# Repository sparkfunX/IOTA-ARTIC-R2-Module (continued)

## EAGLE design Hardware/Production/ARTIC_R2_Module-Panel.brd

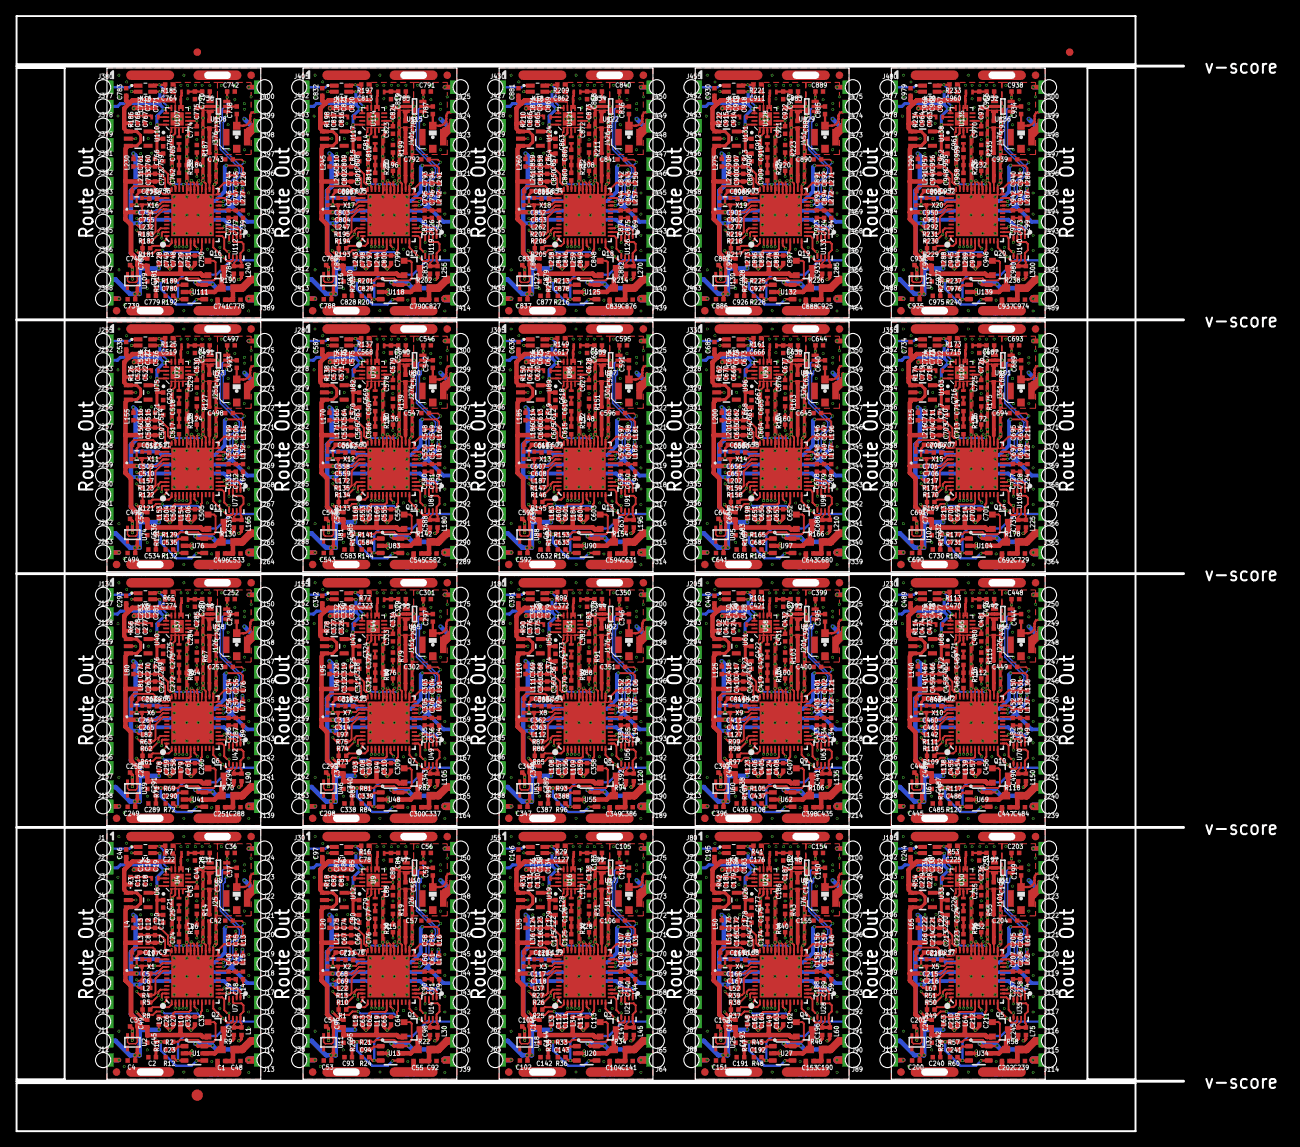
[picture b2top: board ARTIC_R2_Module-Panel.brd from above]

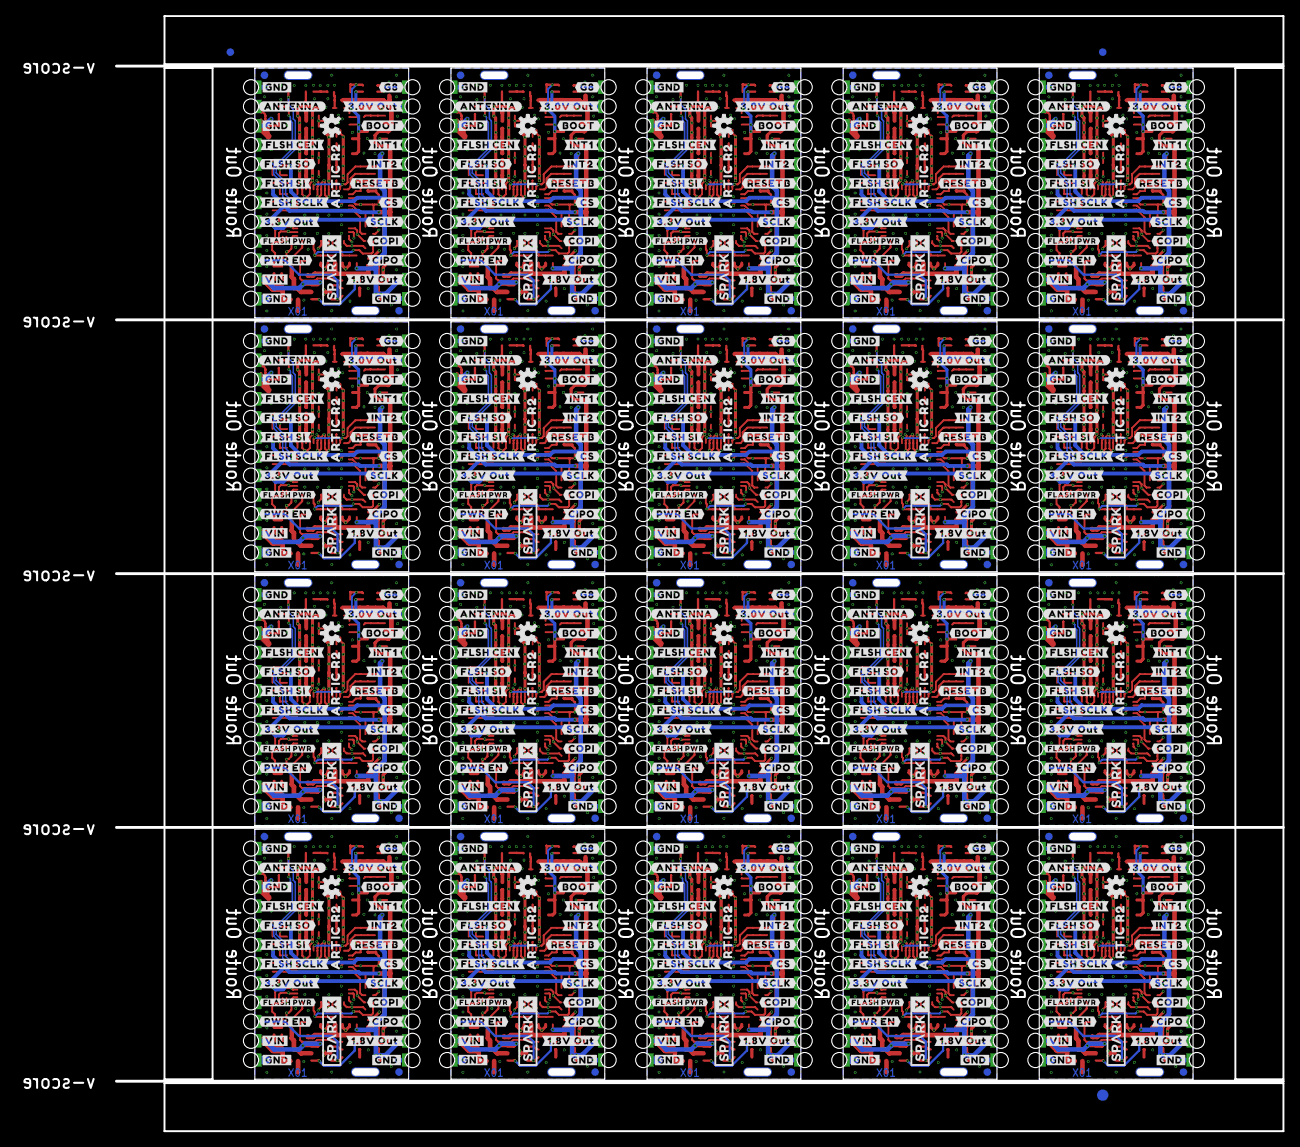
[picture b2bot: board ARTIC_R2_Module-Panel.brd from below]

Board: 4 copper layers, 154.2 x 147.3 mm, 2886 parts (583 on the bottom side), 1140 nets.

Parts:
C1, C15, C16, C20, C44, C45, C55, C80, C82, C86, C89, C95, C104, C129, C131, C135, C138, C144, C153, C178, C180, C184, C187, C193, C202, C227, C229, C233, C236, C242, C251, C276, C278, C282, C285, C291, C300, C325, C327, C331, C334, C340, C349, C374, C376, C380, C383, C389, C398, C423, C425, C429, C432, C438, C447, C472, C474, C478, C481, C487, C496, C521, C523, C527, C530, C536, C545, C570, C572, C576, C579, C585, C594, C619, C621, C625, C628, C634, C643, C668, C670, C674, C677, C683, C692, C717, C719, C723, C726, C732, C741, C766, C768, C772, C775, C781, C790, C815, C817, C821, C824, C830, C839, C864, C866, C870, C873, C879, C888, C913, C915, C919, C922, C928, C937, C962, C964, C968, C971, C977: 2.2uF; 0402-TIGHT
C2, C93, C142, C191, C240, C289, C338, C387, C436, C485, C534, C583, C632, C681, C730, C779, C828, C877, C926, C975: 10nF; 0402-TIGHT
C3, C4, C9, C12, C23, C46, C53, C54, C70, C74, C94, C97, C102, C103, C119, C123, C143, C146, C151, C152, C168, C172, C192, C195, C200, C201, C217, C221, C241, C244, C249, C250, C266, C270, C290, C293, C298, C299, C315, C319, C339, C342, C347, C348, C364, C368, C388, C391, C396, C397, C413, C417, C437, C440, C445, C446, C462, C466, C486, C489, C494, C495, C511, C515, C535, C538, C543, C544, C560, C564, C584, C587, C592, C593, C609, C613, C633, C636, C641, C642, C658, C662, C682, C685, C690, C691, C707, C711, C731, C734, C739, C740, C756, C760, C780, C783, C788, C789, C805, C809, C829, C832, C837, C838, C854, C858, C878, C881, C886, C887, C903, C907, C927, C930, C935, C936, C952, C956, C976, C979: 1.0uF; 0402-TIGHT
C5, C7, C18, C27, C33, C34, C39, C40, C58, C60, C62, C64, C66, C68, C81, C90, C107, C109, C111, C113, C115, C117, C130, C139, C156, C158, C160, C162, C164, C166, C179, C188, C205, C207, C209, C211, C213, C215, C228, C237, C254, C256, C258, C260, C262, C264, C277, C286, C303, C305, C307, C309, C311, C313, C326, C335, C352, C354, C356, C358, C360, C362, C375, C384, C401, C403, C405, C407, C409, C411, C424, C433, C450, C452, C454, C456, C458, C460, C473, C482, C499, C501, C503, C505, C507, C509, C522, C531, C548, C550, C552, C554, C556, C558, C571, C580, C597, C599, C601, C603, C605, C607, C620, C629, C646, C648, C650, C652, C654, C656, C669, C678, C695, C697, C699, C701, C703, C705, C718, C727, C744, C746, C748, C750, C752, C754, C767, C776, C793, C795, C797, C799, C801, C803, C816, C825, C842, C844, C846, C848, C850, C852, C865, C874, C891, C893, C895, C897, C899, C901, C914, C923, C940, C942, C944, C946, C948, C950, C963, C972: 22pF; 0402-TIGHT
C6, C8, C26, C32, C35, C38, C41, C48, C49, C50, C59, C61, C63, C65, C67, C69, C91, C92, C96, C98, C108, C110, C112, C114, C116, C118, C140, C141, C145, C147, C157, C159, C161, C163, C165, C167, C189, C190, C194, C196, C206, C208, C210, C212, C214, C216, C238, C239, C243, C245, C255, C257, C259, C261, C263, C265, C287, C288, C292, C294, C304, C306, C308, C310, C312, C314, C336, C337, C341, C343, C353, C355, C357, C359, C361, C363, C385, C386, C390, C392, C402, C404, C406, C408, C410, C412, C434, C435, C439, C441, C451, C453, C455, C457, C459, C461, C483, C484, C488, C490, C500, C502, C504, C506, C508, C510, C532, C533, C537, C539, C549, C551, C553, C555, C557, C559, C581, C582, C586, C588, C598, C600, C602, C604, C606, C608, C630, C631, C635, C637, C647, C649, C651, C653, C655, C657, C679, C680, C684, C686, C696, C698, C700, C702, C704, C706, C728, C729, C733, C735, C745, C747, C749, C751, C753, C755, C777, C778, C782, C784, C794, C796, C798, C800, C802, C804, C826, C827, C831, C833, C843, C845, C847, C849, C851, C853, C875, C876, C880, C882, C892, C894, C896, C898, C900, C902, C924, C925, C929, C931, C941, C943, C945, C947, C949, C951, C973, C974, C978, C980: 0.1uF; 0402-TIGHT
C10, C71, C120, C169, C218, C267, C316, C365, C414, C463, C512, C561, C610, C659, C708, C757, C806, C855, C904, C953: 47nF; 0402-TIGHT
C11, C19, C21, C22, C24, C25, C30, C31, C36, C37, C42, C43, C47, C51, C52, C56, C57, C73, C76, C77, C78, C79, C85, C88, C99, C100, C101, C105, C106, C122, C125, C126, C127, C128, C134, C137, C148, C149, C150, C154, C155, C171, C174, C175, C176, C177, C183, C186, C197, C198, C199, C203, C204, C220, C223, C224, C225, C226, C232, C235, C246, C247, C248, C252, C253, C269, C272, C273, C274, C275, C281, C284, C295, C296, C297, C301, C302, C318, C321, C322, C323, C324, C330, C333, C344, C345, C346, C350, C351, C367, C370, C371, C372, C373, C379, C382, C393, C394, C395, C399, C400, C416, C419, C420, C421, C422, C428, C431, C442, C443, C444, C448, C449, C465, C468, C469, C470, C471, C477, C480, C491, C492, C493, C497, C498, C514, C517, C518, C519, C520, C526, C529, C540, C541, C542, C546, C547, C563, C566, C567, C568, C569, C575, C578, C589, C590, C591, C595, C596, C612, C615, C616, C617, C618, C624, C627, C638, C639, C640, C644, C645, C661, C664, C665, C666, C667, C673, C676, C687, C688, C689, C693, C694, C710, C713, C714, C715, C716, C722, C725, C736, C737, C738, C742, C743, C759, C762, C763, C764, C765, C771, C774, C785, C786, C787, C791, C792, C808, C811, C812, C813, C814, C820, C823, C834, C835, C836, C840, C841, C857, C860, C861, C862, C863, C869, C872, C883, C884, C885, C889, C890, C906, C909, C910, C911, C912, C918, C921, C932, C933, C934, C938, C939, C955, C958, C959, C960, C961, C967, C970: 100pF; 0402-TIGHT
C13, C14, C75, C87, C124, C136, C173, C185, C222, C234, C271, C283, C320, C332, C369, C381, C418, C430, C467, C479, C516, C528, C565, C577, C614, C626, C663, C675, C712, C724, C761, C773, C810, C822, C859, C871, C908, C920, C957, C969: 10uF; 0402-TIGHT
C17, C72, C121, C170, C219, C268, C317, C366, C415, C464, C513, C562, C611, C660, C709, C758, C807, C856, C905, C954: 1.0nF; 0402-TIGHT
C28, C84, C133, C182, C231, C280, C329, C378, C427, C476, C525, C574, C623, C672, C721, C770, C819, C868, C917, C966: 9.1pF; 0402-TIGHT
C29, C83, C132, C181, C230, C279, C328, C377, C426, C475, C524, C573, C622, C671, C720, C769, C818, C867, C916, C965: 2.4 pF; 0402_MURATA
E$1, E$2, E$3, E$4: FIDUCIAL-1X2
E$5, E$6: FIDUCIAL-1.5X3
FD1, FD2, FD3, FD4, FD5, FD6, FD7, FD8, FD9, FD10, FD11, FD12, FD13, FD14, FD15, FD16, FD17, FD18, FD19, FD20, FD21, FD22, FD23, FD24, FD25, FD26, FD27, FD28, FD29, FD30, FD31, FD32, FD33, FD34, FD35, FD36, FD37, FD38, FD39, FD40, FD41, FD42, FD43, FD44, FD45, FD46, FD47, FD48, FD49, FD50, FD51, FD52, FD53, FD54, FD55, FD56, FD57, FD58, FD59, FD60, FD61, FD62, FD63, FD64, FD65, FD66, FD67, FD68, FD69, FD70, FD71, FD72, FD73, FD74, FD75, FD76, FD77, FD78, FD79, FD80: FIDUCIAL1X2; FIDUCIAL-1X2
J1, J2, J3, J4, J5, J6, J7, J8, J9, J10, J11, J12, J13, J14, J15, J16, J17, J18, J19, J20, J21, J22, J23, J24, J27, J28, J29, J30, J31, J32, J33, J34, J35, J36, J37, J38, J39, J40, J41, J42, J43, J44, J45, J46, J47, J48, J49, J50, J52, J53, J54, J55, J56, J57, J58, J59, J60, J61, J62, J63, J64, J65, J66, J67, J68, J69, J70, J71, J72, J73, J74, J75, J77, J78, J79, J80, J81, J82, J83, J84, J85, J86, J87, J88, J89, J90, J91, J92, J93, J94, J95, J96, J97, J98, J99, J100, J102, J103, J104, J105, J106, J107, J108, J109, J110, J111, J112, J113, J114, J115, J116, J117, J118, J119, J120, J121, J122, J123, J124, J125, J127, J128, J129, J130, J131, J132, J133, J134, J135, J136, J137, J138, J139, J140, J141, J142, J143, J144, J145, J146, J147, J148, J149, J150, J152, J153, J154, J155, J156, J157, J158, J159, J160, J161, J162, J163, J164, J165, J166, J167, J168, J169, J170, J171, J172, J173, J174, J175, J177, J178, J179, J180, J181, J182, J183, J184, J185, J186, J187, J188, J189, J190, J191, J192, J193, J194, J195, J196, J197, J198, J199, J200, J202, J203, J204, J205, J206, J207, J208, J209, J210, J211, J212, J213, J214, J215, J216, J217, J218, J219, J220, J221, J222, J223, J224, J225, J227, J228, J229, J230, J231, J232, J233, J234, J235, J236, J237, J238, J239, J240, J241, J242, J243, J244, J245, J246, J247, J248, J249, J250, J252, J253, J254, J255, J256, J257, J258, J259, J260, J261, J262, J263, J264, J265, J266, J267, J268, J269, J270, J271, J272, J273, J274, J275, J277, J278, J279, J280, J281, J282, J283, J284, J285, J286, J287, J288, J289, J290, J291, J292, J293, J294, J295, J296, J297, J298, J299, J300, J302, J303, J304, J305, J306, J307, J308, J309, J310, J311, J312, J313, J314, J315, J316, J317, J318, J319, J320, J321, J322, J323, J324, J325, J327, J328, J329, J330, J331, J332, J333, J334, J335, J336, J337, J338, J339, J340, J341, J342, J343, J344, J345, J346, J347, J348, J349, J350, J352, J353, J354, J355, J356, J357, J358, J359, J360, J361, J362, J363, J364, J365, J366, J367, J368, J369, J370, J371, J372, J373, J374, J375, J377, J378, J379, J380, J381, J382, J383, J384, J385, J386, J387, J388, J389, J390, J391, J392, J393, J394, J395, J396, J397, J398, J399, J400, J402, J403, J404, J405, J406, J407, J408, J409, J410, J411, J412, J413, J414, J415, J416, J417, J418, J419, J420, J421, J422, J423, J424, J425, J427, J428, J429, J430, J431, J432, J433, J434, J435, J436, J437, J438, J439, J440, J441, J442, J443, J444, J445, J446, J447, J448, J449, J450, J452, J453, J454, J455, J456, J457, J458, J459, J460, J461, J462, J463, J464, J465, J466, J467, J468, J469, J470, J471, J472, J473, J474, J475, J477, J478, J479, J480, J481, J482, J483, J484, J485, J486, J487, J488, J489, J490, J491, J492, J493, J494, J495, J496, J497, J498, J499, J500: CONN_01_CASTELLATED_4LAYER
J25, J26, J51, J76, J101, J126, J151, J176, J201, J226, J251, J276, J301, J326, J351, J376, J401, J426, J451, J476: U.FL
K1, K2, K3, K4, K5, K6, K7, K8, K9, K10, K11, K12, K13, K14, K15, K16, K17, K18, K19, K20: TLP3475R; TLP3475RTPF
L1, L2, L3, L4, L9, L10, L13, L14, L15, L16, L17, L18, L19, L20, L21, L22, L29, L30, L31, L32, L33, L34, L35, L36, L37, L44, L45, L46, L47, L48, L49, L50, L51, L52, L59, L60, L61, L62, L63, L64, L65, L66, L67, L74, L75, L76, L77, L78, L79, L80, L81, L82, L89, L90, L91, L92, L93, L94, L95, L96, L97, L104, L105, L106, L107, L108, L109, L110, L111, L112, L119, L120, L121, L122, L123, L124, L125, L126, L127, L134, L135, L136, L137, L138, L139, L140, L141, L142, L149, L150, L151, L152, L153, L154, L155, L156, L157, L164, L165, L166, L167, L168, L169, L170, L171, L172, L179, L180, L181, L182, L183, L184, L185, L186, L187, L194, L195, L196, L197, L198, L199, L200, L201, L202, L209, L210, L211, L212, L213, L214, L215, L216, L217, L224, L225, L226, L227, L228, L229, L230, L231, L232, L239, L240, L241, L242, L243, L244, L245, L246, L247, L254, L255, L256, L257, L258, L259, L260, L261, L262, L269, L270, L271, L272, L273, L274, L275, L276, L277, L284, L285, L286, L287, L288, L289, L290, L291, L292, L299, L300: 30Ω; 0402-TIGHT
L5, L24, L39, L54, L69, L84, L99, L114, L129, L144, L159, L174, L189, L204, L219, L234, L249, L264, L279, L294: 15nH; 0402_COILCRAFT
L6, L25, L40, L55, L70, L85, L100, L115, L130, L145, L160, L175, L190, L205, L220, L235, L250, L265, L280, L295: 27nH; 0402_COILCRAFT
L7, L23, L38, L53, L68, L83, L98, L113, L128, L143, L158, L173, L188, L203, L218, L233, L248, L263, L278, L293: 18nH; 0402_COILCRAFT
L8, L26, L41, L56, L71, L86, L101, L116, L131, L146, L161, L176, L191, L206, L221, L236, L251, L266, L281, L296: 12nH; 0402_COILCRAFT
L11, L27, L42, L57, L72, L87, L102, L117, L132, L147, L162, L177, L192, L207, L222, L237, L252, L267, L282, L297: 30nH; 0402_COILCRAFT
L12, L28, L43, L58, L73, L88, L103, L118, L133, L148, L163, L178, L193, L208, L223, L238, L253, L268, L283, L298: 51nH; 0402_COILCRAFT
LOGO1, LOGO2, LOGO3, LOGO4, LOGO5, LOGO6, LOGO7, LOGO8, LOGO9, LOGO10, LOGO11, LOGO12, LOGO13, LOGO14, LOGO15, LOGO16, LOGO17, LOGO18, LOGO19, LOGO20: OSHW-LOGOS; OSHW-LOGO-S
Q1, Q2, Q3, Q4, Q5, Q6, Q7, Q8, Q9, Q10, Q11, Q12, Q13, Q14, Q15, Q16, Q17, Q18, Q19, Q20: 5.8A/30V/35mΩ; SOT23-3
R1, R5, R8, R10, R25, R26, R37, R38, R49, R50, R61, R62, R73, R74, R85, R86, R97, R98, R109, R110, R121, R122, R133, R134, R145, R146, R157, R158, R169, R170, R181, R182, R193, R194, R205, R206, R217, R218, R229, R230: 100k; 0402-TIGHT
R2, R11, R21, R23, R33, R35, R45, R47, R57, R59, R69, R71, R81, R83, R93, R95, R105, R107, R117, R119, R129, R131, R141, R143, R153, R155, R165, R167, R177, R179, R189, R191, R201, R203, R213, R215, R225, R227, R237, R239: 100OHM; 0402-TIGHT
R3, R18, R30, R42, R54, R66, R78, R90, R102, R114, R126, R138, R150, R162, R174, R186, R198, R210, R222, R234: 3.9OHM; 0402-TIGHT
R4, R13, R27, R39, R51, R63, R75, R87, R99, R111, R123, R135, R147, R159, R171, R183, R195, R207, R219, R231: 33k; 0402-TIGHT
R6, R15, R28, R40, R52, R64, R76, R88, R100, R112, R124, R136, R148, R160, R172, R184, R196, R208, R220, R232: 220OHM; 0402-TIGHT
R7, R12, R16, R24, R29, R36, R41, R48, R53, R60, R65, R72, R77, R84, R89, R96, R101, R108, R113, R120, R125, R132, R137, R144, R149, R156, R161, R168, R173, R180, R185, R192, R197, R204, R209, R216, R221, R228, R233, R240: 10k; 0402-TIGHT
R9, R22, R34, R46, R58, R70, R82, R94, R106, R118, R130, R142, R154, R166, R178, R190, R202, R214, R226, R238: 0.1R; 0603
R14, R19, R31, R43, R55, R67, R79, R91, R103, R115, R127, R139, R151, R163, R175, R187, R199, R211, R223, R235: 470; 0402-TIGHT
R17, R20, R32, R44, R56, R68, R80, R92, R104, R116, R128, R140, R152, R164, R176, R188, R200, R212, R224, R236: 47; 0402-TIGHT
SCREEN, SCREEN1, SCREEN2, SCREEN3, SCREEN4, SCREEN5, SCREEN6, SCREEN7, SCREEN8, SCREEN9, SCREEN10, SCREEN11, SCREEN12, SCREEN13, SCREEN14, SCREEN15, SCREEN16, SCREEN17, SCREEN18, SCREEN19: ARTIC_R2_CASTELLATED_CAN; ARTIC_R2_CASTELLATED
SPARKX1, SPARKX2, SPARKX3, SPARKX4, SPARKX5, SPARKX6, SPARKX7, SPARKX8, SPARKX9, SPARKX10, SPARKX11, SPARKX12, SPARKX13, SPARKX14, SPARKX15, SPARKX16, SPARKX17, SPARKX18, SPARKX19, SPARKX20: SPARKX-LOGO4; SPARKX-MEDIUM
U1, U13, U20, U27, U34, U41, U48, U55, U62, U69, U76, U83, U90, U97, U104, U111, U118, U125, U132, U139: ADM4210-1; TSOT6
U2, U11, U18, U25, U32, U39, U46, U53, U60, U67, U74, U81, U88, U95, U102, U109, U116, U123, U130, U137: 1.8V/100mA; SC70
U3, U8, U15, U22, U29, U36, U43, U50, U57, U64, U71, U78, U85, U92, U99, U106, U113, U120, U127, U134: ARTIC_R2; QFN-48
U4, U9, U16, U23, U30, U37, U44, U51, U58, U65, U72, U79, U86, U93, U100, U107, U114, U121, U128, U135: RFPA0133; QFN50P300X300X86-17N
U5, U10, U17, U24, U31, U38, U45, U52, U59, U66, U73, U80, U87, U94, U101, U108, U115, U122, U129, U136: AS179-92LF; SOT65P220X100-6N
U6, U12, U19, U26, U33, U40, U47, U54, U61, U68, U75, U82, U89, U96, U103, U110, U117, U124, U131, U138: 3.0V; SOT23-5
U7, U14, U21, U28, U35, U42, U49, U56, U63, U70, U77, U84, U91, U98, U105, U112, U119, U126, U133, U140: SST25VF020BUSON; USON_3X2MM
U$1, U$3, U$4, U$5, U$28, U$29, U$30, U$31, U$54, U$55, U$56, U$57, U$80, U$81, U$82, U$83, U$106, U$107, U$108, U$109, U$132, U$133, U$134, U$135, U$158, U$159, U$160, U$161, U$184, U$185, U$186, U$187, U$210, U$211, U$212, U$213, U$236, U$237, U$238, U$239, U$262, U$263, U$264, U$265, U$288, U$289, U$290, U$291, U$314, U$315, U$316, U$317, U$340, U$341, U$342, U$343, U$366, U$367, U$368, U$369, U$392, U$393, U$394, U$395, U$418, U$419, U$420, U$421, U$444, U$445, U$446, U$447, U$470, U$471, U$472, U$473, U$496, U$497, U$498, U$499: #GND#0
U$2, U$27, U$53, U$79, U$105, U$131, U$157, U$183, U$209, U$235, U$261, U$287, U$313, U$339, U$365, U$391, U$417, U$443, U$469, U$495: 10
U$6, U$32, U$58, U$84, U$110, U$136, U$162, U$188, U$214, U$240, U$266, U$292, U$318, U$344, U$370, U$396, U$422, U$448, U$474, U$500: #PWR_EN#0
U$7, U$33, U$59, U$85, U$111, U$137, U$163, U$189, U$215, U$241, U$267, U$293, U$319, U$345, U$371, U$397, U$423, U$449, U$475, U$501: #VIN#0
U$8, U$52, U$78, U$104, U$130, U$156, U$182, U$208, U$234, U$260, U$286, U$312, U$338, U$364, U$390, U$416, U$442, U$468, U$494, U$520: #FLASH_PWR#0
U$9, U$34, U$60, U$86, U$112, U$138, U$164, U$190, U$216, U$242, U$268, U$294, U$320, U$346, U$372, U$398, U$424, U$450, U$476, U$502: #FLSH_SCLK#0
U$10, U$35, U$61, U$87, U$113, U$139, U$165, U$191, U$217, U$243, U$269, U$295, U$321, U$347, U$373, U$399, U$425, U$451, U$477, U$503: #FLSH_SI#0
U$11, U$37, U$63, U$89, U$115, U$141, U$167, U$193, U$219, U$245, U$271, U$297, U$323, U$349, U$375, U$401, U$427, U$453, U$479, U$505: #FLSH_SO#0
U$12, U$36, U$62, U$88, U$114, U$140, U$166, U$192, U$218, U$244, U$270, U$296, U$322, U$348, U$374, U$400, U$426, U$452, U$478, U$504: #FLSH_CEN#0
U$13, U$38, U$64, U$90, U$116, U$142, U$168, U$194, U$220, U$246, U$272, U$298, U$324, U$350, U$376, U$402, U$428, U$454, U$480, U$506: #3#3V_OUT#0
U$14, U$39, U$65, U$91, U$117, U$143, U$169, U$195, U$221, U$247, U$273, U$299, U$325, U$351, U$377, U$403, U$429, U$455, U$481, U$507: #ANTENNA#0
U$15, U$40, U$66, U$92, U$118, U$144, U$170, U$196, U$222, U$248, U$274, U$300, U$326, U$352, U$378, U$404, U$430, U$456, U$482, U$508: #G8#0
U$16, U$41, U$67, U$93, U$119, U$145, U$171, U$197, U$223, U$249, U$275, U$301, U$327, U$353, U$379, U$405, U$431, U$457, U$483, U$509: #3#0V_OUT#0
U$17, U$42, U$68, U$94, U$120, U$146, U$172, U$198, U$224, U$250, U$276, U$302, U$328, U$354, U$380, U$406, U$432, U$458, U$484, U$510: #BOOT#0
U$18, U$43, U$69, U$95, U$121, U$147, U$173, U$199, U$225, U$251, U$277, U$303, U$329, U$355, U$381, U$407, U$433, U$459, U$485, U$511: #INT1#0
U$19, U$44, U$70, U$96, U$122, U$148, U$174, U$200, U$226, U$252, U$278, U$304, U$330, U$356, U$382, U$408, U$434, U$460, U$486, U$512: #INT2#0
U$20, U$45, U$71, U$97, U$123, U$149, U$175, U$201, U$227, U$253, U$279, U$305, U$331, U$357, U$383, U$409, U$435, U$461, U$487, U$513: #RESETB#0
U$21, U$46, U$72, U$98, U$124, U$150, U$176, U$202, U$228, U$254, U$280, U$306, U$332, U$358, U$384, U$410, U$436, U$462, U$488, U$514: #CS#0
U$22, U$47, U$73, U$99, U$125, U$151, U$177, U$203, U$229, U$255, U$281, U$307, U$333, U$359, U$385, U$411, U$437, U$463, U$489, U$515: #SCLK#0
U$23, U$48, U$74, U$100, U$126, U$152, U$178, U$204, U$230, U$256, U$282, U$308, U$334, U$360, U$386, U$412, U$438, U$464, U$490, U$516: #COPI#0
U$24, U$49, U$75, U$101, U$127, U$153, U$179, U$205, U$231, U$257, U$283, U$309, U$335, U$361, U$387, U$413, U$439, U$465, U$491, U$517: #CIPO#0
U$25, U$50, U$76, U$102, U$128, U$154, U$180, U$206, U$232, U$258, U$284, U$310, U$336, U$362, U$388, U$414, U$440, U$466, U$492, U$518: #1#8V_OUT#0
U$26, U$51, U$77, U$103, U$129, U$155, U$181, U$207, U$233, U$259, U$285, U$311, U$337, U$363, U$389, U$415, U$441, U$467, U$493, U$519: ARTIC_R20
X1, X2, X3, X4, X5, X6, X7, X8, X9, X10, X11, X12, X13, X14, X15, X16, X17, X18, X19, X20: CRYSTAL-TCXO-26MHZ; CRYSTAL-TCXO-SMD-1.65X1.25

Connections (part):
1.8V: C4.1, J11.1, L2.2, L4.2, L9.2, L13.2, L14.2, U2.5
1.8V1: C53.1, J37.1, L16.2, L18.2, L20.2, L22.2, L29.2, U11.5
1.8V2: C102.1, J62.1, L31.2, L33.2, L35.2, L37.2, L44.2, U18.5
1.8V3: C151.1, J87.1, L46.2, L48.2, L50.2, L52.2, L59.2, U25.5
1.8V4: C200.1, J112.1, L61.2, L63.2, L65.2, L67.2, L74.2, U32.5
1.8V5: C249.1, J137.1, L76.2, L78.2, L80.2, L82.2, L89.2, U39.5
1.8V6: C298.1, J162.1, L91.2, L93.2, L95.2, L97.2, L104.2, U46.5
1.8V7: C347.1, J187.1, L106.2, L108.2, L110.2, L112.2, L119.2, U53.5
1.8V8: C396.1, J212.1, L121.2, L123.2, L125.2, L127.2, L134.2, U60.5
1.8V9: C445.1, J237.1, L136.2, L138.2, L140.2, L142.2, L149.2, U67.5
1.8V10: C494.1, J262.1, L151.2, L153.2, L155.2, L157.2, L164.2, U74.5
1.8V11: C543.1, J287.1, L166.2, L168.2, L170.2, L172.2, L179.2, U81.5
1.8V12: C592.1, J312.1, L181.2, L183.2, L185.2, L187.2, L194.2, U88.5
1.8V13: C641.1, J337.1, L196.2, L198.2, L200.2, L202.2, L209.2, U95.5
1.8V14: C690.1, J362.1, L211.2, L213.2, L215.2, L217.2, L224.2, U102.5
1.8V15: C739.1, J387.1, L226.2, L228.2, L230.2, L232.2, L239.2, U109.5
1.8V16: C788.1, J412.1, L241.2, L243.2, L245.2, L247.2, L254.2, U116.5
1.8V17: C837.1, J437.1, L256.2, L258.2, L260.2, L262.2, L269.2, U123.5
1.8V18: C886.1, J462.1, L271.2, L273.2, L275.2, L277.2, L284.2, U130.5
1.8V19: C935.1, J487.1, L286.2, L288.2, L290.2, L292.2, L299.2, U137.5
ANTENNA: C37.1, J23.1, J25.FEED
ANTENNA1: C52.1, J26.FEED, J49.1
ANTENNA2: C101.1, J51.FEED, J74.1
ANTENNA3: C150.1, J76.FEED, J99.1
ANTENNA4: C199.1, J101.FEED, J124.1
ANTENNA5: C248.1, J126.FEED, J149.1
ANTENNA6: C297.1, J151.FEED, J174.1
ANTENNA7: C346.1, J176.FEED, J199.1
ANTENNA8: C395.1, J201.FEED, J224.1
ANTENNA9: C444.1, J226.FEED, J249.1
ANTENNA10: C493.1, J251.FEED, J274.1
ANTENNA11: C542.1, J276.FEED, J299.1
ANTENNA12: C591.1, J301.FEED, J324.1
ANTENNA13: C640.1, J326.FEED, J349.1
ANTENNA14: C689.1, J351.FEED, J374.1
ANTENNA15: C738.1, J376.FEED, J399.1
ANTENNA16: C787.1, J401.FEED, J424.1
ANTENNA17: C836.1, J426.FEED, J449.1
ANTENNA18: C885.1, J451.FEED, J474.1
ANTENNA19: C934.1, J476.FEED, J499.1
BOOT: J3.1, R5.1, U3.46
BOOT1: J28.1, R10.1, U8.46
BOOT2: J53.1, R26.1, U15.46
BOOT3: J78.1, R38.1, U22.46
BOOT4: J103.1, R50.1, U29.46
BOOT5: J128.1, R62.1, U36.46
BOOT6: J153.1, R74.1, U43.46
BOOT7: J178.1, R86.1, U50.46
BOOT8: J203.1, R98.1, U57.46
BOOT9: J228.1, R110.1, U64.46
BOOT10: J253.1, R122.1, U71.46
BOOT11: J278.1, R134.1, U78.46
BOOT12: J303.1, R146.1, U85.46
BOOT13: J328.1, R158.1, U92.46
BOOT14: J353.1, R170.1, U99.46
BOOT15: J378.1, R182.1, U106.46
BOOT16: J403.1, R194.1, U113.46
BOOT17: J428.1, R206.1, U120.46
BOOT18: J453.1, R218.1, U127.46
BOOT19: J478.1, R230.1, U134.46
CIPO: J10.1, U3.5
CIPO1: J36.1, U8.5
CIPO2: J61.1, U15.5
CIPO3: J86.1, U22.5
CIPO4: J111.1, U29.5
CIPO5: J136.1, U36.5
CIPO6: J161.1, U43.5
CIPO7: J186.1, U50.5
CIPO8: J211.1, U57.5
CIPO9: J236.1, U64.5
CIPO10: J261.1, U71.5
CIPO11: J286.1, U78.5
CIPO12: J311.1, U85.5
CIPO13: J336.1, U92.5
CIPO14: J361.1, U99.5
CIPO15: J386.1, U106.5
CIPO16: J411.1, U113.5
CIPO17: J436.1, U120.5
CIPO18: J461.1, U127.5
CIPO19: J486.1, U134.5
COPI: J9.1, U3.4
COPI1: J35.1, U8.4
COPI2: J60.1, U15.4
COPI3: J85.1, U22.4
COPI4: J110.1, U29.4
COPI5: J135.1, U36.4
COPI6: J160.1, U43.4
COPI7: J185.1, U50.4
COPI8: J210.1, U57.4
COPI9: J235.1, U64.4
COPI10: J260.1, U71.4
COPI11: J285.1, U78.4
COPI12: J310.1, U85.4
COPI13: J335.1, U92.4
COPI14: J360.1, U99.4
COPI15: J385.1, U106.4
COPI16: J410.1, U113.4
COPI17: J435.1, U120.4
COPI18: J460.1, U127.4
COPI19: J485.1, U134.4
CS: J7.1, U3.2
CS1: J33.1, U8.2
CS2: J58.1, U15.2
CS3: J83.1, U22.2
CS4: J108.1, U29.2
CS5: J133.1, U36.2
CS6: J158.1, U43.2
CS7: J183.1, U50.2
CS8: J208.1, U57.2
CS9: J233.1, U64.2
CS10: J258.1, U71.2
CS11: J283.1, U78.2
CS12: J308.1, U85.2
CS13: J333.1, U92.2
CS14: J358.1, U99.2
CS15: J383.1, U106.2
CS16: J408.1, U113.2
CS17: J433.1, U120.2
CS18: J458.1, U127.2
CS19: J483.1, U134.2
FLASH_PWR: J16.1, L1.2
FLASH_PWR1: J42.1, L30.2
FLASH_PWR2: J67.1, L45.2
FLASH_PWR3: J92.1, L60.2
FLASH_PWR4: J117.1, L75.2
FLASH_PWR5: J142.1, L90.2
FLASH_PWR6: J167.1, L105.2
FLASH_PWR7: J192.1, L120.2
FLASH_PWR8: J217.1, L135.2
FLASH_PWR9: J242.1, L150.2
FLASH_PWR10: J267.1, L165.2
FLASH_PWR11: J292.1, L180.2
FLASH_PWR12: J317.1, L195.2
FLASH_PWR13: J342.1, L210.2
FLASH_PWR14: J367.1, L225.2
FLASH_PWR15: J392.1, L240.2
FLASH_PWR16: J417.1, L255.2
FLASH_PWR17: J442.1, L270.2
FLASH_PWR18: J467.1, L285.2
FLASH_PWR19: J492.1, L300.2
FLASH_VCC: C50.1, L1.1, U7.3, U7.7, U7.8
FLASH_VCC1: C98.1, L30.1, U14.3, U14.7, U14.8
FLASH_VCC2: C147.1, L45.1, U21.3, U21.7, U21.8
FLASH_VCC3: C196.1, L60.1, U28.3, U28.7, U28.8
FLASH_VCC4: C245.1, L75.1, U35.3, U35.7, U35.8
FLASH_VCC5: C294.1, L90.1, U42.3, U42.7, U42.8
FLASH_VCC6: C343.1, L105.1, U49.3, U49.7, U49.8
FLASH_VCC7: C392.1, L120.1, U56.3, U56.7, U56.8
FLASH_VCC8: C441.1, L135.1, U63.3, U63.7, U63.8
FLASH_VCC9: C490.1, L150.1, U70.3, U70.7, U70.8
FLASH_VCC10: C539.1, L165.1, U77.3, U77.7, U77.8
FLASH_VCC11: C588.1, L180.1, U84.3, U84.7, U84.8
FLASH_VCC12: C637.1, L195.1, U91.3, U91.7, U91.8
FLASH_VCC13: C686.1, L210.1, U98.3, U98.7, U98.8
FLASH_VCC14: C735.1, L225.1, U105.3, U105.7, U105.8
FLASH_VCC15: C784.1, L240.1, U112.3, U112.7, U112.8
FLASH_VCC16: C833.1, L255.1, U119.3, U119.7, U119.8
FLASH_VCC17: C882.1, L270.1, U126.3, U126.7, U126.8
FLASH_VCC18: C931.1, L285.1, U133.3, U133.7, U133.8
FLASH_VCC19: C980.1, L300.1, U140.3, U140.7, U140.8
FLSH_CEN: J21.1, U3.15, U7.1
FLSH_CEN1: J47.1, U8.15, U14.1
FLSH_CEN2: J72.1, U15.15, U21.1
FLSH_CEN3: J97.1, U22.15, U28.1
FLSH_CEN4: J122.1, U29.15, U35.1
FLSH_CEN5: J147.1, U36.15, U42.1
FLSH_CEN6: J172.1, U43.15, U49.1
FLSH_CEN7: J197.1, U50.15, U56.1
FLSH_CEN8: J222.1, U57.15, U63.1
FLSH_CEN9: J247.1, U64.15, U70.1
FLSH_CEN10: J272.1, U71.15, U77.1
FLSH_CEN11: J297.1, U78.15, U84.1
FLSH_CEN12: J322.1, U85.15, U91.1
FLSH_CEN13: J347.1, U92.15, U98.1
FLSH_CEN14: J372.1, U99.15, U105.1
FLSH_CEN15: J397.1, U106.15, U112.1
FLSH_CEN16: J422.1, U113.15, U119.1
FLSH_CEN17: J447.1, U120.15, U126.1
FLSH_CEN18: J472.1, U127.15, U133.1
FLSH_CEN19: J497.1, U134.15, U140.1
FLSH_SCLK: J18.1, U3.12, U7.6
FLSH_SCLK1: J44.1, U8.12, U14.6
FLSH_SCLK2: J69.1, U15.12, U21.6
FLSH_SCLK3: J94.1, U22.12, U28.6
FLSH_SCLK4: J119.1, U29.12, U35.6
FLSH_SCLK5: J144.1, U36.12, U42.6
FLSH_SCLK6: J169.1, U43.12, U49.6
FLSH_SCLK7: J194.1, U50.12, U56.6
FLSH_SCLK8: J219.1, U57.12, U63.6
FLSH_SCLK9: J244.1, U64.12, U70.6
FLSH_SCLK10: J269.1, U71.12, U77.6
FLSH_SCLK11: J294.1, U78.12, U84.6
FLSH_SCLK12: J319.1, U85.12, U91.6
FLSH_SCLK13: J344.1, U92.12, U98.6
FLSH_SCLK14: J369.1, U99.12, U105.6
FLSH_SCLK15: J394.1, U106.12, U112.6
FLSH_SCLK16: J419.1, U113.12, U119.6
FLSH_SCLK17: J444.1, U120.12, U126.6
FLSH_SCLK18: J469.1, U127.12, U133.6
FLSH_SCLK19: J494.1, U134.12, U140.6
FLSH_SI: J19.1, U3.13, U7.5
FLSH_SI1: J45.1, U8.13, U14.5
FLSH_SI2: J70.1, U15.13, U21.5
FLSH_SI3: J95.1, U22.13, U28.5
FLSH_SI4: J120.1, U29.13, U35.5
FLSH_SI5: J145.1, U36.13, U42.5
FLSH_SI6: J170.1, U43.13, U49.5
FLSH_SI7: J195.1, U50.13, U56.5
FLSH_SI8: J220.1, U57.13, U63.5
FLSH_SI9: J245.1, U64.13, U70.5
FLSH_SI10: J270.1, U71.13, U77.5
FLSH_SI11: J295.1, U78.13, U84.5
FLSH_SI12: J320.1, U85.13, U91.5
FLSH_SI13: J345.1, U92.13, U98.5
FLSH_SI14: J370.1, U99.13, U105.5
FLSH_SI15: J395.1, U106.13, U112.5
FLSH_SI16: J420.1, U113.13, U119.5
FLSH_SI17: J445.1, U120.13, U126.5
FLSH_SI18: J470.1, U127.13, U133.5
FLSH_SI19: J495.1, U134.13, U140.5
FLSH_SO: J20.1, U3.14, U7.2
FLSH_SO1: J46.1, U8.14, U14.2
FLSH_SO2: J71.1, U15.14, U21.2
FLSH_SO3: J96.1, U22.14, U28.2
FLSH_SO4: J121.1, U29.14, U35.2
FLSH_SO5: J146.1, U36.14, U42.2
FLSH_SO6: J171.1, U43.14, U49.2
FLSH_SO7: J196.1, U50.14, U56.2
FLSH_SO8: J221.1, U57.14, U63.2
FLSH_SO9: J246.1, U64.14, U70.2
FLSH_SO10: J271.1, U71.14, U77.2
FLSH_SO11: J296.1, U78.14, U84.2
FLSH_SO12: J321.1, U85.14, U91.2
FLSH_SO13: J346.1, U92.14, U98.2
FLSH_SO14: J371.1, U99.14, U105.2
FLSH_SO15: J396.1, U106.14, U112.2
FLSH_SO16: J421.1, U113.14, U119.2
FLSH_SO17: J446.1, U120.14, U126.2
FLSH_SO18: J471.1, U127.14, U133.2
FLSH_SO19: J496.1, U134.14, U140.2
G1: J30.1, K2.1
G2: J55.1, K3.1
G3: J80.1, K4.1
G4: J105.1, K5.1
G5: J130.1, K6.1
G6: J155.1, K7.1
G7: J180.1, K8.1
G8: J1.1, K1.1
G9: J205.1, K9.1
G10: J230.1, K10.1
G11: J255.1, K11.1
G12: J280.1, K12.1
G13: J305.1, K13.1
G14: J330.1, K14.1
G15: J355.1, K15.1
G16: J380.1, K16.1
G17: J405.1, K17.1
G18: J430.1, K18.1
G19: J455.1, K19.1
G20: J480.1, K20.1
GND: C1.2, C2.2, C3.2, C4.2, C5.2, C6.2, C7.2, C8.2, C9.2, C10.2, C11.2, C12.2, C13.2, C14.2, C15.2, C16.2, C18.2, C19.2, C20.1, C21.1, C22.1, C23.2, C26.2, C27.2, C28.1, C32.2, C33.2, C34.2, C35.2, C36.2, C38.2, C39.2, C40.2, C41.2, C42.2, C43.1, C44.2, C45.2, C46.2, C48.2, C49.2, C50.2, J12.1, J13.1, J22.1, J24.1, J25.1, J25.2, K1.2, L11.P$1, L12.P$1, R4.2, R6.1, R7.2, R12.2, R14.1, SCREEN.1-1, SCREEN.1-16, SCREEN.2, SCREEN.3-1, SCREEN.3-16, SCREEN.4, U1.2, U2.2, U3.25, U3.27, U3.29, U3.30, U3.31, U3.32, U3.39, U3.GND, U4.2, U4.EDAP, U5.2, U6.2, U7.4, X1.1, X1.2
GND1: C53.2, C54.2, C55.2, C56.2, C57.2, C58.2, C59.2, C60.2, C61.2, C62.2, C63.2, C64.2, C65.2, C66.2, C67.2, C68.2, C69.2, C70.2, C71.2, C73.2, C74.2, C75.2, C78.1, C79.1, C80.1, C81.2, C82.2, C84.1, C85.2, C86.2, C87.2, C88.1, C89.2, C90.2, C91.2, C92.2, C93.2, C94.2, C95.2, C96.2, C97.2, C98.2, J26.1, J26.2, J38.1, J39.1, J48.1, J50.1, K2.2, L27.P$1, L28.P$1, R13.2, R15.1, R16.2, R19.1, R24.2, SCREEN1.1-1, SCREEN1.1-16, SCREEN1.2, SCREEN1.3-1, SCREEN1.3-16, SCREEN1.4, U8.25, U8.27, U8.29, U8.30, U8.31, U8.32, U8.39, U8.GND, U9.2, U9.EDAP, U10.2, U11.2, U12.2, U13.2, U14.4, X2.1, X2.2
GND2: C102.2, C103.2, C104.2, C105.2, C106.2, C107.2, C108.2, C109.2, C110.2, C111.2, C112.2, C113.2, C114.2, C115.2, C116.2, C117.2, C118.2, C119.2, C120.2, C122.2, C123.2, C124.2, C127.1, C128.1, C129.1, C130.2, C131.2, C133.1, C134.2, C135.2, C136.2, C137.1, C138.2, C139.2, C140.2, C141.2, C142.2, C143.2, C144.2, C145.2, C146.2, C147.2, J51.1, J51.2, J63.1, J64.1, J73.1, J75.1, K3.2, L42.P$1, L43.P$1, R27.2, R28.1, R29.2, R31.1, R36.2, SCREEN2.1-1, SCREEN2.1-16, SCREEN2.2, SCREEN2.3-1, SCREEN2.3-16, SCREEN2.4, U15.25, U15.27, U15.29, U15.30, U15.31, U15.32, U15.39, U15.GND, U16.2, U16.EDAP, U17.2, U18.2, U19.2, U20.2, U21.4, X3.1, X3.2
GND3: C151.2, C152.2, C153.2, C154.2, C155.2, C156.2, C157.2, C158.2, C159.2, C160.2, C161.2, C162.2, C163.2, C164.2, C165.2, C166.2, C167.2, C168.2, C169.2, C171.2, C172.2, C173.2, C176.1, C177.1, C178.1, C179.2, C180.2, C182.1, C183.2, C184.2, C185.2, C186.1, C187.2, C188.2, C189.2, C190.2, C191.2, C192.2, C193.2, C194.2, C195.2, C196.2, J76.1, J76.2, J88.1, J89.1, J98.1, J100.1, K4.2, L57.P$1, L58.P$1, R39.2, R40.1, R41.2, R43.1, R48.2, SCREEN3.1-1, SCREEN3.1-16, SCREEN3.2, SCREEN3.3-1, SCREEN3.3-16, SCREEN3.4, U22.25, U22.27, U22.29, U22.30, U22.31, U22.32, U22.39, U22.GND, U23.2, U23.EDAP, U24.2, U25.2, U26.2, U27.2, U28.4, X4.1, X4.2
GND4: C200.2, C201.2, C202.2, C203.2, C204.2, C205.2, C206.2, C207.2, C208.2, C209.2, C210.2, C211.2, C212.2, C213.2, C214.2, C215.2, C216.2, C217.2, C218.2, C220.2, C221.2, C222.2, C225.1, C226.1, C227.1, C228.2, C229.2, C231.1, C232.2, C233.2, C234.2, C235.1, C236.2, C237.2, C238.2, C239.2, C240.2, C241.2, C242.2, C243.2, C244.2, C245.2, J101.1, J101.2, J113.1, J114.1, J123.1, J125.1, K5.2, L72.P$1, L73.P$1, R51.2, R52.1, R53.2, R55.1, R60.2, SCREEN4.1-1, SCREEN4.1-16, SCREEN4.2, SCREEN4.3-1, SCREEN4.3-16, SCREEN4.4, U29.25, U29.27, U29.29, U29.30, U29.31, U29.32, U29.39, U29.GND, U30.2, U30.EDAP, U31.2, U32.2, U33.2, U34.2, U35.4, X5.1, X5.2
GND5: C249.2, C250.2, C251.2, C252.2, C253.2, C254.2, C255.2, C256.2, C257.2, C258.2, C259.2, C260.2, C261.2, C262.2, C263.2, C264.2, C265.2, C266.2, C267.2, C269.2, C270.2, C271.2, C274.1, C275.1, C276.1, C277.2, C278.2, C280.1, C281.2, C282.2, C283.2, C284.1, C285.2, C286.2, C287.2, C288.2, C289.2, C290.2, C291.2, C292.2, C293.2, C294.2, J126.1, J126.2, J138.1, J139.1, J148.1, J150.1, K6.2, L87.P$1, L88.P$1, R63.2, R64.1, R65.2, R67.1, R72.2, SCREEN5.1-1, SCREEN5.1-16, SCREEN5.2, SCREEN5.3-1, SCREEN5.3-16, SCREEN5.4, U36.25, U36.27, U36.29, U36.30, U36.31, U36.32, U36.39, U36.GND, U37.2, U37.EDAP, U38.2, U39.2, U40.2, U41.2, U42.4, X6.1, X6.2
GND6: C298.2, C299.2, C300.2, C301.2, C302.2, C303.2, C304.2, C305.2, C306.2, C307.2, C308.2, C309.2, C310.2, C311.2, C312.2, C313.2, C314.2, C315.2, C316.2, C318.2, C319.2, C320.2, C323.1, C324.1, C325.1, C326.2, C327.2, C329.1, C330.2, C331.2, C332.2, C333.1, C334.2, C335.2, C336.2, C337.2, C338.2, C339.2, C340.2, C341.2, C342.2, C343.2, J151.1, J151.2, J163.1, J164.1, J173.1, J175.1, K7.2, L102.P$1, L103.P$1, R75.2, R76.1, R77.2, R79.1, R84.2, SCREEN6.1-1, SCREEN6.1-16, SCREEN6.2, SCREEN6.3-1, SCREEN6.3-16, SCREEN6.4, U43.25, U43.27, U43.29, U43.30, U43.31, U43.32, U43.39, U43.GND, U44.2, U44.EDAP, U45.2, U46.2, U47.2, U48.2, U49.4, X7.1, X7.2
GND7: C347.2, C348.2, C349.2, C350.2, C351.2, C352.2, C353.2, C354.2, C355.2, C356.2, C357.2, C358.2, C359.2, C360.2, C361.2, C362.2, C363.2, C364.2, C365.2, C367.2, C368.2, C369.2, C372.1, C373.1, C374.1, C375.2, C376.2, C378.1, C379.2, C380.2, C381.2, C382.1, C383.2, C384.2, C385.2, C386.2, C387.2, C388.2, C389.2, C390.2, C391.2, C392.2, J176.1, J176.2, J188.1, J189.1, J198.1, J200.1, K8.2, L117.P$1, L118.P$1, R87.2, R88.1, R89.2, R91.1, R96.2, SCREEN7.1-1, SCREEN7.1-16, SCREEN7.2, SCREEN7.3-1, SCREEN7.3-16, SCREEN7.4, U50.25, U50.27, U50.29, U50.30, U50.31, U50.32, U50.39, U50.GND, U51.2, U51.EDAP, U52.2, U53.2, U54.2, U55.2, U56.4, X8.1, X8.2
GND8: C396.2, C397.2, C398.2, C399.2, C400.2, C401.2, C402.2, C403.2, C404.2, C405.2, C406.2, C407.2, C408.2, C409.2, C410.2, C411.2, C412.2, C413.2, C414.2, C416.2, C417.2, C418.2, C421.1, C422.1, C423.1, C424.2, C425.2, C427.1, C428.2, C429.2, C430.2, C431.1, C432.2, C433.2, C434.2, C435.2, C436.2, C437.2, C438.2, C439.2, C440.2, C441.2, J201.1, J201.2, J213.1, J214.1, J223.1, J225.1, K9.2, L132.P$1, L133.P$1, R99.2, R100.1, R101.2, R103.1, R108.2, SCREEN8.1-1, SCREEN8.1-16, SCREEN8.2, SCREEN8.3-1, SCREEN8.3-16, SCREEN8.4, U57.25, U57.27, U57.29, U57.30, U57.31, U57.32, U57.39, U57.GND, U58.2, U58.EDAP, U59.2, U60.2, U61.2, U62.2, U63.4, X9.1, X9.2
GND9: C445.2, C446.2, C447.2, C448.2, C449.2, C450.2, C451.2, C452.2, C453.2, C454.2, C455.2, C456.2, C457.2, C458.2, C459.2, C460.2, C461.2, C462.2, C463.2, C465.2, C466.2, C467.2, C470.1, C471.1, C472.1, C473.2, C474.2, C476.1, C477.2, C478.2, C479.2, C480.1, C481.2, C482.2, C483.2, C484.2, C485.2, C486.2, C487.2, C488.2, C489.2, C490.2, J226.1, J226.2, J238.1, J239.1, J248.1, J250.1, K10.2, L147.P$1, L148.P$1, R111.2, R112.1, R113.2, R115.1, R120.2, SCREEN9.1-1, SCREEN9.1-16, SCREEN9.2, SCREEN9.3-1, SCREEN9.3-16, SCREEN9.4, U64.25, U64.27, U64.29, U64.30, U64.31, U64.32, U64.39, U64.GND, U65.2, U65.EDAP, U66.2, U67.2, U68.2, U69.2, U70.4, X10.1, X10.2
GND10: C494.2, C495.2, C496.2, C497.2, C498.2, C499.2, C500.2, C501.2, C502.2, C503.2, C504.2, C505.2, C506.2, C507.2, C508.2, C509.2, C510.2, C511.2, C512.2, C514.2, C515.2, C516.2, C519.1, C520.1, C521.1, C522.2, C523.2, C525.1, C526.2, C527.2, C528.2, C529.1, C530.2, C531.2, C532.2, C533.2, C534.2, C535.2, C536.2, C537.2, C538.2, C539.2, J251.1, J251.2, J263.1, J264.1, J273.1, J275.1, K11.2, L162.P$1, L163.P$1, R123.2, R124.1, R125.2, R127.1, R132.2, SCREEN10.1-1, SCREEN10.1-16, SCREEN10.2, SCREEN10.3-1, SCREEN10.3-16, SCREEN10.4, U71.25, U71.27, U71.29, U71.30, U71.31, U71.32, U71.39, U71.GND, U72.2, U72.EDAP, U73.2, U74.2, U75.2, U76.2, U77.4, X11.1, X11.2
GND11: C543.2, C544.2, C545.2, C546.2, C547.2, C548.2, C549.2, C550.2, C551.2, C552.2, C553.2, C554.2, C555.2, C556.2, C557.2, C558.2, C559.2, C560.2, C561.2, C563.2, C564.2, C565.2, C568.1, C569.1, C570.1, C571.2, C572.2, C574.1, C575.2, C576.2, C577.2, C578.1, C579.2, C580.2, C581.2, C582.2, C583.2, C584.2, C585.2, C586.2, C587.2, C588.2, J276.1, J276.2, J288.1, J289.1, J298.1, J300.1, K12.2, L177.P$1, L178.P$1, R135.2, R136.1, R137.2, R139.1, R144.2, SCREEN11.1-1, SCREEN11.1-16, SCREEN11.2, SCREEN11.3-1, SCREEN11.3-16, SCREEN11.4, U78.25, U78.27, U78.29, U78.30, U78.31, U78.32, U78.39, U78.GND, U79.2, U79.EDAP, U80.2, U81.2, U82.2, U83.2, U84.4, X12.1, X12.2
GND12: C592.2, C593.2, C594.2, C595.2, C596.2, C597.2, C598.2, C599.2, C600.2, C601.2, C602.2, C603.2, C604.2, C605.2, C606.2, C607.2, C608.2, C609.2, C610.2, C612.2, C613.2, C614.2, C617.1, C618.1, C619.1, C620.2, C621.2, C623.1, C624.2, C625.2, C626.2, C627.1, C628.2, C629.2, C630.2, C631.2, C632.2, C633.2, C634.2, C635.2, C636.2, C637.2, J301.1, J301.2, J313.1, J314.1, J323.1, J325.1, K13.2, L192.P$1, L193.P$1, R147.2, R148.1, R149.2, R151.1, R156.2, SCREEN12.1-1, SCREEN12.1-16, SCREEN12.2, SCREEN12.3-1, SCREEN12.3-16, SCREEN12.4, U85.25, U85.27, U85.29, U85.30, U85.31, U85.32, U85.39, U85.GND, U86.2, U86.EDAP, U87.2, U88.2, U89.2, U90.2, U91.4, X13.1, X13.2
GND13: C641.2, C642.2, C643.2, C644.2, C645.2, C646.2, C647.2, C648.2, C649.2, C650.2, C651.2, C652.2, C653.2, C654.2, C655.2, C656.2, C657.2, C658.2, C659.2, C661.2, C662.2, C663.2, C666.1, C667.1, C668.1, C669.2, C670.2, C672.1, C673.2, C674.2, C675.2, C676.1, C677.2, C678.2, C679.2, C680.2, C681.2, C682.2, C683.2, C684.2, C685.2, C686.2, J326.1, J326.2, J338.1, J339.1, J348.1, J350.1, K14.2, L207.P$1, L208.P$1, R159.2, R160.1, R161.2, R163.1, R168.2, SCREEN13.1-1, SCREEN13.1-16, SCREEN13.2, SCREEN13.3-1, SCREEN13.3-16, SCREEN13.4, U92.25, U92.27, U92.29, U92.30, U92.31, U92.32, U92.39, U92.GND, U93.2, U93.EDAP, U94.2, U95.2, U96.2, U97.2, U98.4, X14.1, X14.2
GND14: C690.2, C691.2, C692.2, C693.2, C694.2, C695.2, C696.2, C697.2, C698.2, C699.2, C700.2, C701.2, C702.2, C703.2, C704.2, C705.2, C706.2, C707.2, C708.2, C710.2, C711.2, C712.2, C715.1, C716.1, C717.1, C718.2, C719.2, C721.1, C722.2, C723.2, C724.2, C725.1, C726.2, C727.2, C728.2, C729.2, C730.2, C731.2, C732.2, C733.2, C734.2, C735.2, J351.1, J351.2, J363.1, J364.1, J373.1, J375.1, K15.2, L222.P$1, L223.P$1, R171.2, R172.1, R173.2, R175.1, R180.2, SCREEN14.1-1, SCREEN14.1-16, SCREEN14.2, SCREEN14.3-1, SCREEN14.3-16, SCREEN14.4, U99.25, U99.27, U99.29, U99.30, U99.31, U99.32, U99.39, U99.GND, U100.2, U100.EDAP, U101.2, U102.2, U103.2, U104.2, U105.4, X15.1, X15.2
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
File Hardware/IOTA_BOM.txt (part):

Partlist exported from C:/Users/pc235/Documents/EAGLE/SparkFun_ARTIC_R2_Module/X01/ARTIC_R2_Module.sch at 07/09/2021 12:30

Part    Value                            Device                                Package                    Description                                                         DESCRIPTION                                              DESIGNER DIGIKEY_PART                      MANUFACTURER_NAME MANUFACTURER_PART MANUFACTURER_PART_NUMBER MANU_PART                MOUSER_PART          MOUSER_PART_NUMBER MOUSER_PRICE-STOCK                                                PACKAGE   PROD_ID     REV VALUE        
C1      2.2uF                            2.2UF-0402_TIGHT-10V-10%-X5R          0402-TIGHT                 2.2µF ceramic capacitors                                                                                                                                                                                                                                                                                                                                                          CAP-14232       2.2uF        
C2      10nF                             10NF-0402T-25V-10%                    0402-TIGHT                 0.01uF/10nF/10,000pF ceramic capacitors                                                                                                                                                                                                                                                                                                                                           CAP-14847       10nF         
C3      1.0uF                            1.0UF-0402T-16V-10%                   0402-TIGHT                 1µF ceramic capacitors                                                                                                                                                                                                                                                                                                                                                            CAP-12417       1.0uF        
C4      1.0uF                            1.0UF-0402T-16V-10%                   0402-TIGHT                 1µF ceramic capacitors                                                                                                                                                                                                                                                                                                                                                            CAP-12417       1.0uF        
C5      22pF                             22PF-0402T-16V-10%                    0402-TIGHT                 22pF ceramic capacitors                                                                                                                                                                                                                                                                                                                                                           CAP-14674       22pF         
C6      0.1uF                            0.1UF-0402T-6.3V-10%-X7R              0402-TIGHT                 0.1µF ceramic capacitors                                                                                                                                                                                                                                                                                                                                                          CAP-14993       0.1uF        
C7      22pF                             22PF-0402T-16V-10%                    0402-TIGHT                 22pF ceramic capacitors                                                                                                                                                                                                                                                                                                                                                           CAP-14674       22pF         
C8      0.1uF                            0.1UF-0402T-6.3V-10%-X7R              0402-TIGHT                 0.1µF ceramic capacitors                                                                                                                                                                                                                                                                                                                                                          CAP-14993       0.1uF        
C9      1.0uF                            1.0UF-0402T-16V-10%                   0402-TIGHT                 1µF ceramic capacitors                                                                                                                                                                                                                                                                                                                                                            CAP-12417       1.0uF        
C10     47nF                             47NF-0402_TIGHT-25V-10%-X7R           0402-TIGHT                 47nF ceramic capacitors                                                                                                                                                                                                                                                                                                                                                           CAP-14243       47nF         
C11     100pF                            100PF-0402T-50V-5%                    0402-TIGHT                 100pF/0.1nF ceramic capacitors                                                                                                                                                                                                                                                                                                                                                    CAP-13458       100pF        
C12     1.0uF                            1.0UF-0402T-16V-10%                   0402-TIGHT                 1µF ceramic capacitors                                                                                                                                                                                                                                                                                                                                                            CAP-12417       1.0uF        
C13     10uF                             10UF-0402T-6.3V-20%                   0402-TIGHT                 10.0µF ceramic capacitors                                                                                                                                                                                                                                                                                                                                                         CAP-14848       10uF         
C14     10uF                             10UF-0402T-6.3V-20%                   0402-TIGHT                 10.0µF ceramic capacitors                                                                                                                                                                                                                                                                                                                                                         CAP-14848       10uF         
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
